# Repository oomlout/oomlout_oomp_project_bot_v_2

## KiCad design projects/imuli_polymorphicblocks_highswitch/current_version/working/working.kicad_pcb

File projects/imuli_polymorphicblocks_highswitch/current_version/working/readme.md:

# polymorphicblocks
 
## summary 
* id: imuli_polymorphicblocks_highswitch
* user: imuli
* name: polymorphicblocks
* board: highswitch
* repo: https://github.com/imuli/PolymorphicBlocks
* src_file_repo_kicad_pcb: examples/HighSwitch/HighSwitch.kicad_pcb
* src_file_repo_kicad_pcb_link: https://github.com/imuli/PolymorphicBlocks/tree/master/examples/HighSwitch/HighSwitch.kicad_pcb

* src_file_repo_sch: 
* src_file_repo_sch_link: https://github.com/imuli/PolymorphicBlocks/tree/master/
* full details link: https://github.com/oomlout/oomlout_oomp_project_bot_v_2/tree/main/projects/imuli_polymorphicblocks_highswitch/current_version/working

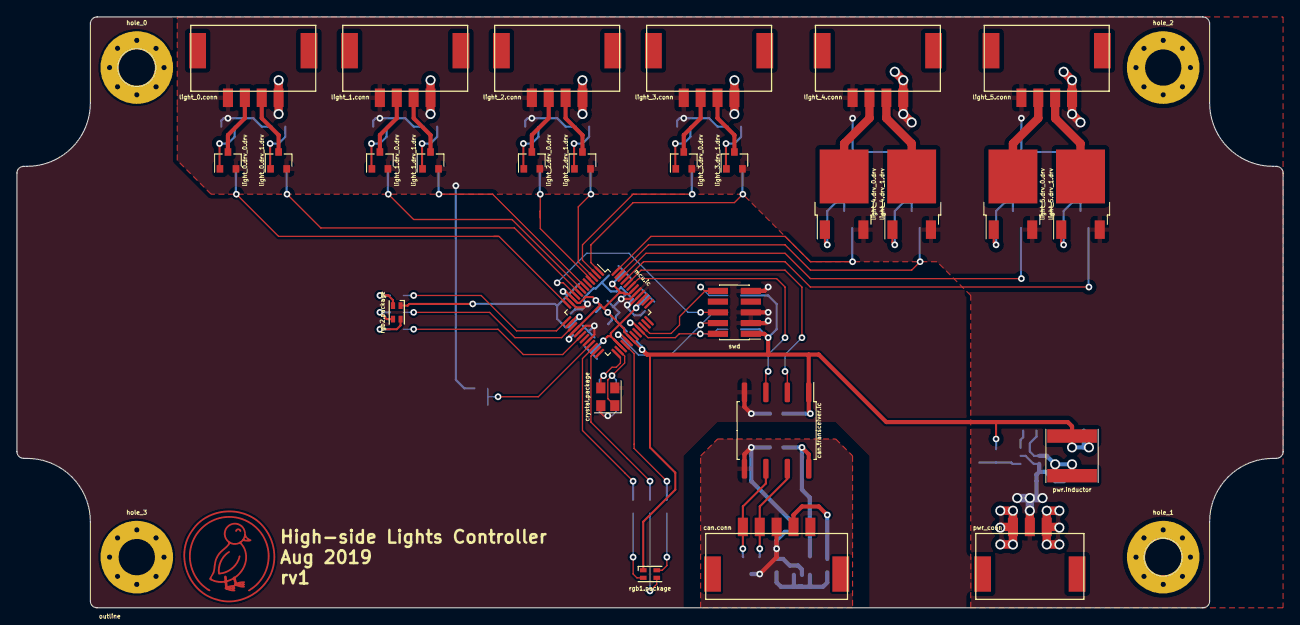
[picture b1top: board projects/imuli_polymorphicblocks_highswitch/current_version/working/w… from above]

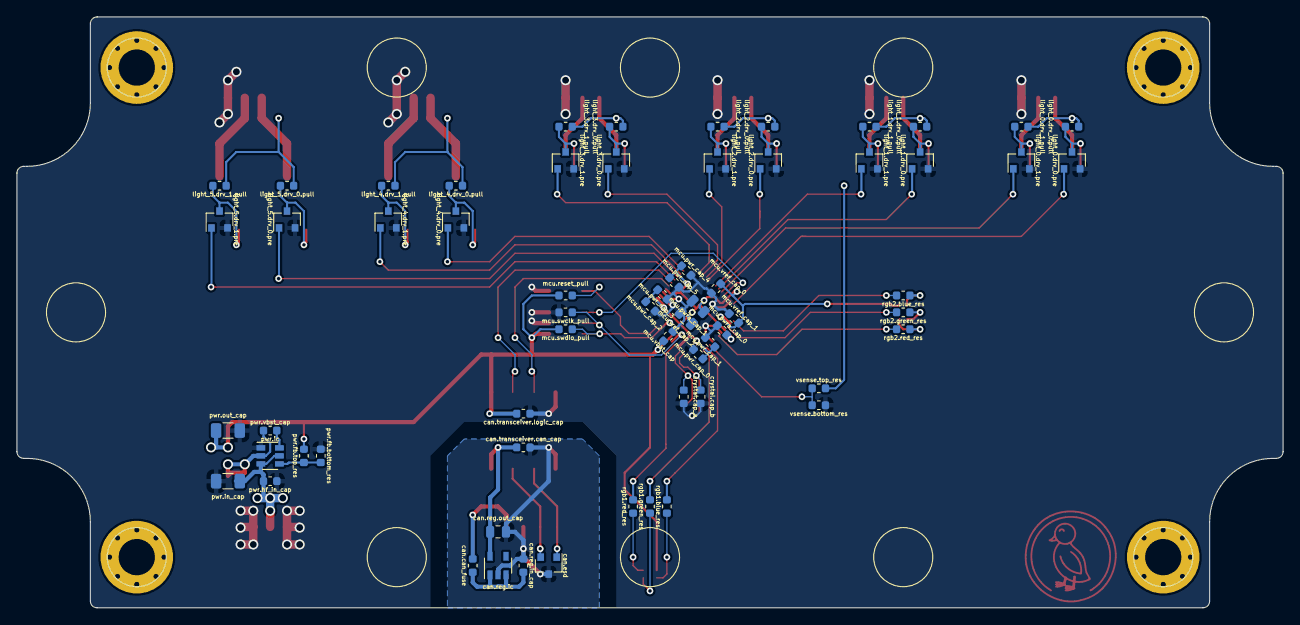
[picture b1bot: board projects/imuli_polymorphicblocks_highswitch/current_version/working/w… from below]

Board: 2 copper layers, 150.0 x 70.0 mm, 96 parts (63 on the bottom side), 69 nets.

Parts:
can.can_fuse: 0ZCM0005FF2G; R_0603_1608Metric
can.conn: Duraclik; Molex_DuraClik_vert_5pin
can.esd: PESD1CAN,215; SOT-23
can.reg.ic: AP2204K-5.0; SOT-23-5
can.reg.in_cap: 1µF, 25V, CL10A105KA8NNNC (C=(8.8e-07, 1.32e-06) 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; C_0603_1608Metric
can.reg.out_cap: 2.2µF, 10V, CL21B225KPFNNNE (C=(1.76e-06, 2.64e-0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; C_0805_2012Metric
can.transceiver.can_cap, can.transceiver.logic_cap: 0.1µF, 50V, CL10B104KB8NNNC (C=(8e-08, 1.2e-07) F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; C_0603_1608Metric
can.transceiver.ic: ISO1050DUB; SOP-8_6.62x9.15mm_P2.54mm
crystal.cap_a, crystal.cap_b: 18pF, 50V, CL10C180FB8NNNC (C=(1.764e-11, 1.836e-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; C_0603_1608Metric
crystal.package: 7V-12.000MAHE-T; Oscillator_SMD_Abracon_ASE-4Pin_3.2x2.5mm
duck: Duck; Duckling
hole_0, hole_1, hole_2, hole_3: M4; MountingHole_4.3mm_M4_Pad_Via
light_0.conn, light_1.conn, light_2.conn, light_3.conn, light_4.conn, light_5.conn: Duraclik; Molex_DuraClik_vert_4pin
light_0.drv_0.drv, light_0.drv_1.drv, light_1.drv_0.drv, light_1.drv_1.drv, light_2.drv_0.drv, light_2.drv_1.drv, light_3.drv_0.drv, light_3.drv_1.drv: DMP3099L-7 (Vds=(10.8, 13.200000000000001) V, Ids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; SOT-23
light_0.drv_0.pre, light_0.drv_1.pre, light_1.drv_0.pre, light_1.drv_1.pre, light_2.drv_0.pre, light_2.drv_1.pre, light_3.drv_0.pre, light_3.drv_1.pre, light_4.drv_0.pre, light_4.drv_1.pre, light_5.drv_0.pre, light_5.drv_1.pre: NX138AKR (Vds=(10.8, 13.200000000000001) V, Ids=(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; SOT-23
light_0.drv_0.pull, light_0.drv_1.pull, light_1.drv_0.pull, light_1.drv_1.pull, light_2.drv_0.pull, light_2.drv_1.pull, light_3.drv_0.pull, light_3.drv_1.pull, light_4.drv_0.pull, light_4.drv_1.pull, light_5.drv_0.pull, light_5.drv_1.pull: 10000, 1%, 0.1W (R=(9900.0, 10100.0) Ohm, P=(0.0,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; R_0603_1608Metric
light_4.drv_0.drv, light_4.drv_1.drv, light_5.drv_0.drv, light_5.drv_1.drv: TSM7P06CP ROG (Vds=(10.8, 13.200000000000001) V, 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; TO-252-2
mcu.ic: LPC1549JBD48; LQFP-48_7x7mm_P0.5mm
mcu.pwr_cap_0, mcu.pwr_cap_2, mcu.pwr_cap_4, mcu.pwra_cap_0, mcu.vbat_cap, mcu.vref_cap_0, mcu.vref_cap_1: 0.1µF, 50V, CL10B104KB8NNNC (C=(8e-08, 1.2e-07) F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; C_0603_1608Metric
mcu.pwr_cap_1, mcu.pwr_cap_3, mcu.pwr_cap_5: 10000pF, 50V, CL10B103KB8NNNC (C=(8e-09, 1.2e-08)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; C_0603_1608Metric
mcu.pwra_cap_1, mcu.vref_cap_2: 10µF, 10V, CL21A106KPFNNNG (C=(8e-06, 1.199999999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; C_0805_2012Metric
mcu.reset_pull: 10000, 1%, 0.1W (R=(9500.0, 10500.0) Ohm, P=(0.0,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; R_0603_1608Metric
mcu.swclk_pull, mcu.swdio_pull: 10000, 1%, 0.1W (R=(9500.0, 105000.0) Ohm, P=(0.0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; R_0603_1608Metric
outline: PN1332_Panel; Outline_150mm_70mm_PNX-91432
pwr.fb.bottom_res: 10000, 1%, 0.1W (R=(9900.0, 10100.0) Ohm, P=(0.0,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; R_0603_1608Metric
pwr.fb.top_res: 33000, 1%, 0.1W (R=(32670.0, 33330.0) Ohm, P=(0.0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; R_0603_1608Metric
pwr.hf_in_cap, pwr.vbst_cap: 0.1µF, 50V, CL10B104KB8NNNC (C=(8e-08, 1.2e-07) F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; C_0603_1608Metric
pwr.ic: TPS561201; SOT-23-6
pwr.in_cap: 22µF, 16V, CL31A226MOCLNNC (C=(7.498403575989784e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; C_1206_3216Metric
pwr.inductor: 10µH, 2.5A, NR6045T100M (L=(4.6396372126436784e-0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; L_Taiyo-Yuden_NR-60xx
pwr.out_cap: 22µF, 6.3V, CL31A226MQHNNNE (C=(1.034482758620689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; C_1206_3216Metric
pwr_conn: Duraclik; Molex_DuraClik_vert_3pin
rgb1.blue_res, rgb1.green_res, rgb1.red_res, rgb2.blue_res, rgb2.green_res, rgb2.red_res: 1000, 1%, 0.1W (R=(950.0, 1050.0) Ohm, P=(0.0, 0.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; R_0603_1608Metric
rgb1.package, rgb2.package: LED_RGB_0606
swd: SWD; PinHeader_2x05_P1.27mm_Vertical_SMD
vsense.bottom_res: 1500, 1%, 0.1W (R=(1485.0, 1515.0) Ohm, P=(0.0, 0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; R_0603_1608Metric
vsense.top_res: 4700, 1%, 0.1W (R=(4653.0, 4747.0) Ohm, P=(0.0, 0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; R_0603_1608Metric

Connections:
can.can.canh: can.conn.4, can.esd.2, can.transceiver.ic.7
can.can.canl: can.conn.5, can.esd.1, can.transceiver.ic.6
can.can_gnd: can.conn.3, can.esd.3, can.reg.ic.2, can.reg.in_cap.2, can.reg.out_cap.2, can.transceiver.can_cap.2, can.transceiver.ic.5
can.can_pwr: can.can_fuse.1, can.conn.2
can.controller.txd: can.transceiver.ic.3, mcu.ic.43
can.reg.pwr_in: can.can_fuse.2, can.reg.ic.1, can.reg.ic.3, can.reg.in_cap.1
can.reg.pwr_out: can.reg.ic.5, can.reg.out_cap.1, can.transceiver.can_cap.1, can.transceiver.ic.8
crystal.crystal.b: crystal.cap_b.1, crystal.package.3, mcu.ic.25
gnd: can.transceiver.ic.4, can.transceiver.logic_cap.2, crystal.cap_a.2, crystal.cap_b.2, crystal.package.2, crystal.package.4, light_0.conn.4, light_0.drv_0.pre.2, light_0.drv_1.pre.2, light_1.conn.4, light_1.drv_0.pre.2, light_1.drv_1.pre.2, light_2.conn.4, light_2.drv_0.pre.2, light_2.drv_1.pre.2, light_3.conn.4, light_3.drv_0.pre.2, light_3.drv_1.pre.2, light_4.conn.4, light_4.drv_0.pre.2, light_4.drv_1.pre.2, light_5.conn.4, light_5.drv_0.pre.2, light_5.drv_1.pre.2, mcu.ic.11, mcu.ic.17, mcu.ic.20, mcu.ic.40, mcu.ic.41, mcu.pwr_cap_0.2, mcu.pwr_cap_1.2, mcu.pwr_cap_2.2, mcu.pwr_cap_3.2, mcu.pwr_cap_4.2, mcu.pwr_cap_5.2, mcu.pwra_cap_0.2, mcu.pwra_cap_1.2, mcu.swclk_pull.1, mcu.vbat_cap.2, mcu.vref_cap_0.2, mcu.vref_cap_1.2, mcu.vref_cap_2.2, pwr.fb.bottom_res.2, pwr.hf_in_cap.2, pwr.ic.1, pwr.in_cap.2, pwr.out_cap.2, pwr_conn.1, pwr_conn.3, swd.3, swd.5, swd.9, vsense.bottom_res.2
light_0.conn.out_0: light_0.conn.2, light_0.drv_0.drv.3
light_0.control_0: light_0.drv_0.pre.1, mcu.ic.12
light_0.drv_0.drv.gate: light_0.drv_0.drv.1, light_0.drv_0.pre.3, light_0.drv_0.pull.2
light_0.drv_1.output: light_0.conn.3, light_0.drv_1.drv.3
light_0.drv_1.pull.2: light_0.drv_1.drv.1, light_0.drv_1.pre.3, light_0.drv_1.pull.2
light_1.conn.out_0: light_1.conn.2, light_1.drv_0.drv.3
light_1.conn.out_1: light_1.conn.3, light_1.drv_1.drv.3
light_1.control_0: light_1.drv_0.pre.1, mcu.ic.7
light_1.drv_0.drv.gate: light_1.drv_0.drv.1, light_1.drv_0.pre.3, light_1.drv_0.pull.2
light_1.drv_1.drv.1: light_1.drv_1.drv.1, light_1.drv_1.pre.3, light_1.drv_1.pull.2
light_2.conn.out_1: light_2.conn.3, light_2.drv_1.drv.3
light_2.control_1: light_2.drv_1.pre.1, mcu.ic.3
light_2.drv_0.output: light_2.conn.2, light_2.drv_0.drv.3
light_2.drv_0.pull.2: light_2.drv_0.drv.1, light_2.drv_0.pre.3, light_2.drv_0.pull.2
light_2.drv_1.drv.gate: light_2.drv_1.drv.1, light_2.drv_1.pre.3, light_2.drv_1.pull.2
light_3.conn.3: light_3.conn.3, light_3.drv_1.drv.3
light_3.drv_0.output: light_3.conn.2, light_3.drv_0.drv.3
light_3.drv_0.pre.drain: light_3.drv_0.drv.1, light_3.drv_0.pre.3, light_3.drv_0.pull.2
light_3.drv_1.drv.1: light_3.drv_1.drv.1, light_3.drv_1.pre.3, light_3.drv_1.pull.2
light_4.conn.out_1: light_4.conn.3, light_4.drv_1.drv.2
light_4.control_0: light_4.drv_0.pre.1, mcu.ic.48
light_4.drv_0.drv.gate: light_4.drv_0.drv.1, light_4.drv_0.pre.3, light_4.drv_0.pull.2
light_4.drv_0.output: light_4.conn.2, light_4.drv_0.drv.2
light_4.drv_1.drv.1: light_4.drv_1.drv.1, light_4.drv_1.pre.3, light_4.drv_1.pull.2
light_5.conn.2: light_5.conn.2, light_5.drv_0.drv.2
light_5.conn.out_1: light_5.conn.3, light_5.drv_1.drv.2
light_5.control_0: light_5.drv_0.pre.1, mcu.ic.46
light_5.control_1: light_5.drv_1.pre.1, mcu.ic.45
light_5.drv_0.pull.b: light_5.drv_0.drv.1, light_5.drv_0.pre.3, light_5.drv_0.pull.2
light_5.drv_1.pre.3: light_5.drv_1.drv.1, light_5.drv_1.pre.3, light_5.drv_1.pull.2
mcu.can_0.rxd: can.transceiver.ic.2, mcu.ic.44
mcu.digital_4: light_4.drv_1.pre.1, mcu.ic.47
mcu.digital_6: light_3.drv_1.pre.1, mcu.ic.1
mcu.digital_7: light_3.drv_0.pre.1, mcu.ic.2
mcu.digital_9: light_2.drv_0.pre.1, mcu.ic.4
mcu.digital_10: light_1.drv_1.pre.1, mcu.ic.6
mcu.digital_12: light_0.drv_1.pre.1, mcu.ic.8
mcu.digital_15: mcu.ic.15, rgb2.green_res.2
mcu.digital_16: mcu.ic.18, rgb2.red_res.2
mcu.digital_18: mcu.ic.23, rgb1.green_res.2
mcu.xtal.xtal_in: crystal.cap_a.1, crystal.package.1, mcu.ic.26
pwr.ic.4: pwr.fb.bottom_res.1, pwr.fb.top_res.2, pwr.ic.4
pwr.sw: pwr.ic.2, pwr.inductor.1, pwr.vbst_cap.2
pwr.vbst_cap.1: pwr.ic.6, pwr.vbst_cap.1
rgb1.blue: mcu.ic.22, rgb1.blue_res.2
rgb1.blue_res.a: rgb1.blue_res.1, rgb1.package.2
rgb1.package.3: rgb1.green_res.1, rgb1.package.3
rgb1.package.4: rgb1.package.4, rgb1.red_res.1
rgb1.red: mcu.ic.28, rgb1.red_res.2
rgb2.blue: mcu.ic.13, rgb2.blue_res.2
rgb2.blue_res.a: rgb2.blue_res.1, rgb2.package.2
rgb2.package.3: rgb2.green_res.1, rgb2.package.3
rgb2.package.4: rgb2.package.4, rgb2.red_res.1
swd.2: mcu.ic.33, mcu.swdio_pull.2, swd.2
swd.4: mcu.ic.29, mcu.swclk_pull.2, swd.4
swd.6: mcu.ic.9, swd.6
swd.10: mcu.ic.34, mcu.reset_pull.2, swd.10
v3v3: can.transceiver.ic.1, can.transceiver.logic_cap.1, mcu.ic.10, mcu.ic.14, mcu.ic.16, mcu.ic.27, mcu.ic.30, mcu.ic.39, mcu.ic.42, mcu.pwr_cap_0.1, mcu.pwr_cap_1.1, mcu.pwr_cap_2.1, mcu.pwr_cap_3.1, mcu.pwr_cap_4.1, mcu.pwr_cap_5.1, mcu.pwra_cap_0.1, mcu.pwra_cap_1.1, mcu.reset_pull.1, mcu.swdio_pull.1, mcu.vbat_cap.1, mcu.vref_cap_0.1, mcu.vref_cap_1.1, mcu.vref_cap_2.1, pwr.fb.top_res.1, pwr.inductor.2, pwr.out_cap.1, rgb1.package.1, rgb2.package.1, swd.1
vin: light_0.conn.1, light_0.drv_0.drv.2, light_0.drv_0.pull.1, light_0.drv_1.drv.2, light_0.drv_1.pull.1, light_1.conn.1, light_1.drv_0.drv.2, light_1.drv_0.pull.1, light_1.drv_1.drv.2, light_1.drv_1.pull.1, light_2.conn.1, light_2.drv_0.drv.2, light_2.drv_0.pull.1, light_2.drv_1.drv.2, light_2.drv_1.pull.1, light_3.conn.1, light_3.drv_0.drv.2, light_3.drv_0.pull.1, light_3.drv_1.drv.2, light_3.drv_1.pull.1, light_4.conn.1, light_4.drv_0.drv.3, light_4.drv_0.pull.1, light_4.drv_1.drv.3, light_4.drv_1.pull.1, light_5.conn.1, light_5.drv_0.drv.3, light_5.drv_0.pull.1, light_5.drv_1.drv.3, light_5.drv_1.pull.1, pwr.hf_in_cap.1, pwr.ic.3, pwr.ic.5, pwr.in_cap.1, pwr_conn.2, vsense.top_res.1
vsense.out: mcu.ic.21, vsense.bottom_res.1, vsense.top_res.2

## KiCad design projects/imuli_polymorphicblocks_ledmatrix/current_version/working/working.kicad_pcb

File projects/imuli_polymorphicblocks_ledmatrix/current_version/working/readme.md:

# polymorphicblocks
 
## summary 
* id: imuli_polymorphicblocks_ledmatrix
* user: imuli
* name: polymorphicblocks
* board: ledmatrix
* repo: https://github.com/imuli/PolymorphicBlocks
* src_file_repo_kicad_pcb: examples/LedMatrix/LedMatrix.kicad_pcb
* src_file_repo_kicad_pcb_link: https://github.com/imuli/PolymorphicBlocks/tree/master/examples/LedMatrix/LedMatrix.kicad_pcb

* src_file_repo_sch: 
* src_file_repo_sch_link: https://github.com/imuli/PolymorphicBlocks/tree/master/
* full details link: https://github.com/oomlout/oomlout_oomp_project_bot_v_2/tree/main/projects/imuli_polymorphicblocks_ledmatrix/current_version/working

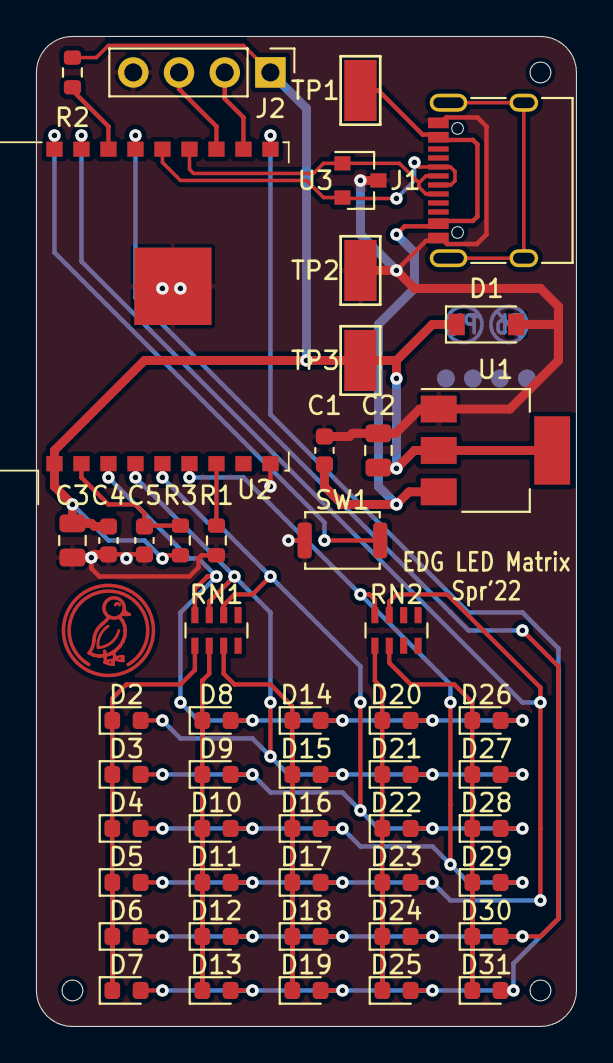
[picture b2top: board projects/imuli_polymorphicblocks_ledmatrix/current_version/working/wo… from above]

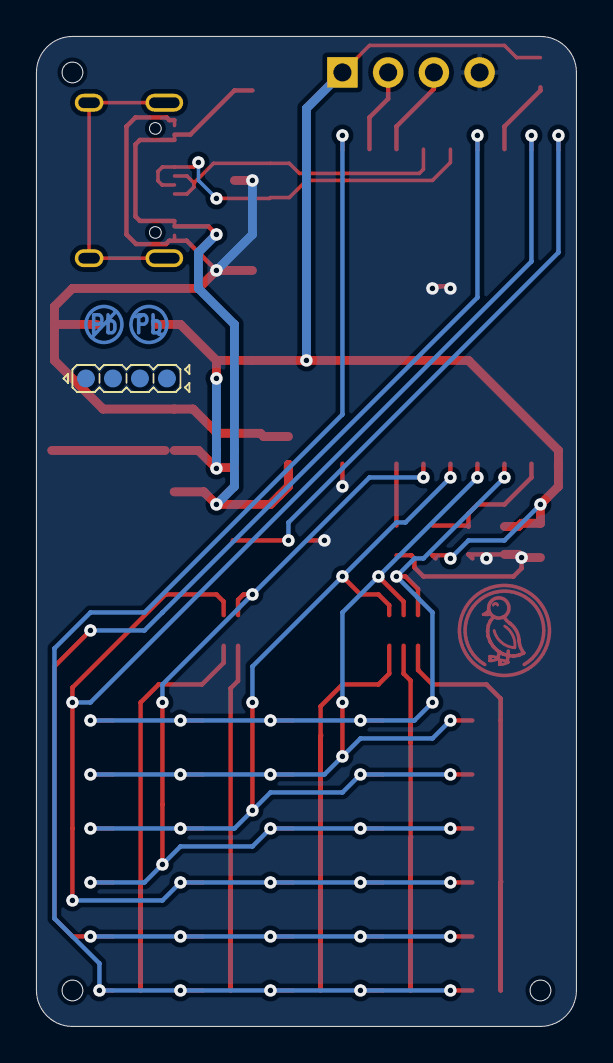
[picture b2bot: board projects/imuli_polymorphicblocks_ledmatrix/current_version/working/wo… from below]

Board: 2 copper layers, 30.0 x 55.0 mm, 56 parts (2 on the bottom side), 23 nets.

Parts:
1: Indicator_LeadFree
2: Indicator_IdDots_4
C1, C4: C14663; C_0603_1608Metric
C2: C1779; C_0805_2012Metric
C3: C15850; C_0805_2012Metric
C5: C15849; C_0603_1608Metric
D1: C499796; D_SOD-123
D2, D3, D4, D5, D6, D7, D8, D9, D10, D11, D12, D13, D14, D15, D16, D17, D18, D19, D20, D21, D22, D23, D24, D25, D26, D27, D28, D29, D30, D31: C72038; LED_0603_1608Metric
H1, H2, H3: JlcToolingHole_1.152mm
J1: C165948; USB_C_Receptacle_XKB_U262-16XN-4BVC11
J2: PinHeader_1x04_P2.54mm_Vertical
R1, R2, R3: C25804; R_0603_1608Metric
RN1, RN2: C425057; R_Array_Concave_4x0603
SW1: SW_Push_SPST_NO_Alps_SKRK
TP1, TP2, TP3: C238130; TestPoint_Keystone_5015_Micro-Minature
U1: C86781; SOT-223-3_TabPin2
U2: C2934560; ESP-WROOM-02
U3: C87911; SOT-23
U4: Symbol_Duckling

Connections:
gnd: C1.2, C2.2, C3.2, C4.2, C5.2, D1.2, J1.A1, J1.A12, J1.B1, J1.B12, J2.4, R1.1, SW1.1, TP2.1, U1.1, U2.9, U2.19, U3.3
matrix.ios.5: D6.2, D12.2, D18.2, D24.2, D30.2, U2.15
matrix.ios.6: D7.2, D13.2, D19.2, D25.2, D31.2, U2.10
matrix_res1.a.0: D2.1, D3.1, D4.1, D5.1, D6.1, D7.1, RN1.1
matrix_res1.a.1: D8.1, D9.1, D10.1, D11.1, D12.1, D13.1, RN1.2
matrix_res1.a.2: D14.1, D15.1, D16.1, D17.1, D18.1, D19.1, RN1.3
matrix_res1.b.1: D2.2, D15.2, D21.2, D27.2, RN1.7, U2.4
matrix_res2.a.0: D20.1, D21.1, D22.1, D23.1, D24.1, D25.1, RN2.1
matrix_res2.a.1: D26.1, D27.1, D28.1, D29.1, D30.1, D31.1, RN2.2
mcu.en_pull.output: C5.1, R3.2, U2.2
mcu.gpio.led_0: D8.2, D14.2, D20.2, D26.2, RN1.8, U2.3
mcu.gpio.led_2: D3.2, D9.2, D22.2, D28.2, RN1.6, U2.5
mcu.gpio.led_3: D4.2, D10.2, D16.2, D29.2, RN2.8, U2.6
mcu.gpio.led_4: D5.2, D11.2, D17.2, D23.2, RN2.7, U2.17
mcu.gpio.sw1: SW1.2, U2.18
mcu.ic.uart0.rx: J2.2, U2.11
mcu.io2_pull.io: R2.2, U2.16
mcu.io8_pull.b: R1.2, U2.7
mcu.uart0.uart.rx: J2.3, U2.12
usb.usb.dp: J1.A6, J1.B6, U2.14, U3.2
usb_esd.usb.dm: J1.A7, J1.B7, U2.13, U3.1
v3v3: C2.1, C3.1, C4.1, D1.1, J2.1, R2.1, R3.1, TP3.1, U1.2, U2.1
vusb: C1.1, J1.A4, J1.A9, J1.B4, J1.B9, TP1.1, U1.3

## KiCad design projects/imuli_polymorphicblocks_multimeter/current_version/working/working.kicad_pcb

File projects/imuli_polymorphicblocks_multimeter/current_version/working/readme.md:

# polymorphicblocks
 
## summary 
* id: imuli_polymorphicblocks_multimeter
* user: imuli
* name: polymorphicblocks
* board: multimeter
* repo: https://github.com/imuli/PolymorphicBlocks
* src_file_repo_kicad_pcb: examples/Multimeter/Multimeter.kicad_pcb
* src_file_repo_kicad_pcb_link: https://github.com/imuli/PolymorphicBlocks/tree/master/examples/Multimeter/Multimeter.kicad_pcb

* src_file_repo_sch: 
* src_file_repo_sch_link: https://github.com/imuli/PolymorphicBlocks/tree/master/
* full details link: https://github.com/oomlout/oomlout_oomp_project_bot_v_2/tree/main/projects/imuli_polymorphicblocks_multimeter/current_version/working

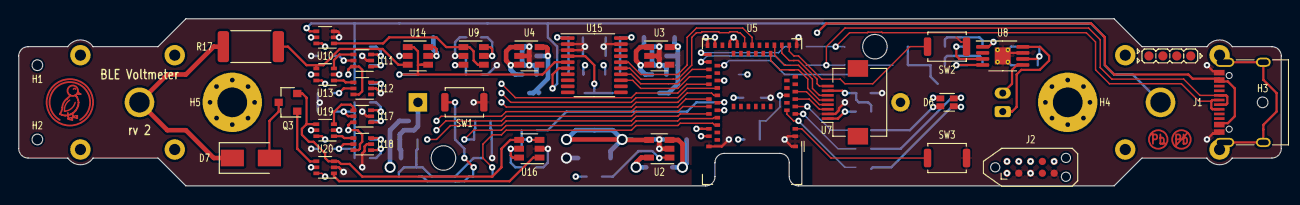
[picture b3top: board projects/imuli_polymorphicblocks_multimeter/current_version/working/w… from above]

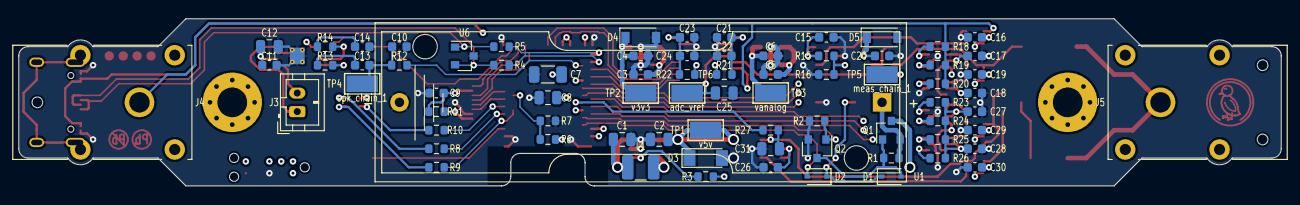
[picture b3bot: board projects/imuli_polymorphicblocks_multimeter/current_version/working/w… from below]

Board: 4 copper layers, 136.0 x 18.0 mm, 111 parts (76 on the bottom side), 80 nets.

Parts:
1: LeadFree; Indicator_LeadFree
2: IdDots4; Indicator_IdDots_4
C1, C8, C25: X5R 25V ±10% 10uF 0805 Multilayer Ceramic Capacit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; C_0805_2012Metric
C2, C12: 25V 4.7uF X5R ±10% 0805 Multilayer Ceramic Capaci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; C_0805_2012Metric
C3, C4, C5, C6, C9, C13, C14: 50V 1uF X5R ±10% 0603 Multilayer Ceramic Capacito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; C_0603_1608Metric
C7: 50V 10uF X5R ±10% 1206 Multilayer Ceramic Capacit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; C_1206_3216Metric
C10: 50V 47nF X7R ±10% 0603 Multilayer Ceramic Capacit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; C_0603_1608Metric
C11, C15, C16, C17, C18, C19, C20, C21, C22, C23, C24, C26, C27, C28, C29, C30: 50V 100nF X7R ±10% 0603 Multilayer Ceramic Capaci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; C_0603_1608Metric
C31: 50V 2.2uF Y5V ±20% 0805 Multilayer Ceramic Capaci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; C_0805_2012Metric
D1, D2: 30V 370mV@1mA 30mA SOD-323 Schottky Barrier Diode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; D_SOD-323
D3: 100nA@1V 25Ω Single 5.2V~{6V} 500mW 5.6V LL-34 Ze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; D_MiniMELF
D4, D5: 5μA@1V 90Ω Single 3.6V~{3.8V} 350mW 3.4V SOD-123 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; D_SOD-123
D6: LED_LiteOn_LTST-C19HE1WT
D7: DIODE GEN PURP 400V 1A DO214AC; D_SMA
H1, H2, H3: JlcToolingHole_1.152mm
H4, H5: M3; MountingHole_3.2mm_M3_Pad_Via
J1: USB_C_Receptacle_XKB_U262-16XN-4BVC11
J2: SWD; Tag-Connect_TC2050-IDC-NL_2x05_P1.27mm_Vertical
J3: JST_PH_B2B-PH-K_1x02_P2.00mm_Vertical
J4, J5: CLIFF_FCR7350
L1: 620mA 22uH ±10% 270mΩ 1210 Inductors (SMD) ROHS; L_1210_3225Metric
Q1: 20V 3.1A 860mW 112mΩ@4.5V,2.8A 1V@250μA P Channel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; SOT-23
Q2: 60V 115mA 200mW 7.5Ω@10V,500mA 2.5V@250μA N Chann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; SOT-23
Q3: MOSFET P-CH 250V 140MA SC-59-3; SOT-23
R1, R2, R3, R6, R7, R8, R9, R10, R12, R13, R14, R15, R16, R18, R19, R20, R23, R24, R25, R26, R27: ±1% 1/10W Thick Film Resistors 75V ±100ppm/℃ -55℃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; R_0603_1608Metric
R4, R5, R11: ±1% 1/10W Thick Film Resistors 75V ±200ppm/℃ -55℃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; R_0603_1608Metric
R17: 1M, 1%, 1.0 W; R_2512_6332Metric
R21, R22: ±1% 1/10W Thick Film Resistors 75V ±400ppm/℃ -55℃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; R_0603_1608Metric
SW1, SW2, SW3: SW_Push_SPST_NO_Alps_SKRK
TP1: v5v; TestPoint_Keystone_5015_Micro-Minature
TP2: v3v3; TestPoint_Keystone_5015_Micro-Minature
TP3: vanalog; TestPoint_Keystone_5015_Micro-Minature
TP4: spk_chain_1; TestPoint_Keystone_5015_Micro-Minature
TP5: meas_chain_1; TestPoint_Keystone_5015_Micro-Minature
TP6: adc_vref; TestPoint_Keystone_5015_Micro-Minature
U1: BatteryHolder_Keystone_2460_1xAA
U2, U3, U4: SOT-23-5
U5: Raytac_MDBT50Q
U6: SOT-23
U7: Hirose_FH12-8S-0.5SH_1x08-1MP_P0.50mm_Horizontal
U8: MSOP-8-1EP_3x3mm_P0.65mm_EP1.73x1.85mm_ThermalVias
U9, U14, U16: SOT-23-6
U10, U11, U12, U13, U17, U18, U19, U20: SOT-363_SC-70-6
U15: TSSOP-20_4.4x6.5mm_P0.65mm
U21: Duck; Symbol_Duckling

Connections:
(adapter)inp.port.src: D7.1, J5.1, R17.1
adc.dvdd_res.b: C23.1, C24.1, R22.2, U15.20
adc.ic.avdd: C21.1, C22.1, R21.2, U15.1
adc.spi.miso: U5.24, U15.16
adc.spi.mosi: U5.26, U15.15
adc.spi.sck: U5.37, U15.14
adc_vref: C25.1, TP6.1, U15.4
data_usb.A4: C7.1, J1.A4, J1.A9, J1.B4, J1.B9, U5.32
data_usb.usb.dm: J1.A7, J1.B7, R5.2, U6.1
data_usb.usb.dp: J1.A6, J1.B6, R4.2, U6.2
driver.control: C31.1, R27.2, U16.3
driver.fet.drain: D7.2, Q3.3
driver.range.switch.inputs.0: R23.2, U17.3
driver.range.switch.inputs.1: R24.2, U17.1
driver.range.switch.inputs.2: R25.2, U18.3
driver.range.switch.inputs.3: R26.2, U18.1
driver.range.switch.sw[1_0].inputs.0: U17.4, U19.3
driver.range.switch.sw[1_0].inputs.1: U18.4, U19.1
driver.select.0_0: U5.46, U17.6, U18.6
driver.sw.inputs.0: Q3.2, U16.4, U19.4, U20.3
driver.sw.inputs.1: U16.1, U20.1
driver.sw.out: Q3.1, U20.4
gate.amp_fet.drain: D1.2, Q1.1, Q2.3, R1.2
gate.ctl_diode.cathode: D1.1, D2.1, SW1.2
gate.pwr_out: C1.1, L1.1, Q1.3, R3.1, R6.1, U2.3
gnd: C1.2, C2.2, C3.2, C4.2, C5.2, C6.2, C7.2, C8.2, C9.2, C10.2, C11.2, C12.2, C14.2, C15.2, C16.2, C17.2, C18.2, C19.2, C20.2, C21.2, C22.2, C23.2, C24.2, C25.2, C26.2, C27.2, C28.2, C29.2, C30.2, C31.2, D3.2, D4.2, D5.2, J1.A1, J1.A12, J1.B1, J1.B12, J2.2, J2.3, J2.5, Q2.2, R2.2, R7.2, R16.2, SW1.1, SW2.1, SW3.1, U1.2, U2.2, U3.2, U4.2, U5.1, U5.2, U5.15, U5.33, U5.55, U6.3, U7.2, U8.7, U8.9, U9.2, U10.2, U10.3, U11.2, U12.2, U13.2, U14.2, U15.2, U15.3, U15.19, U16.2, U17.2, U18.2, U19.2, U20.2
inn_merge.inputs.0: J4.1, R18.1, R19.1, R20.1, U10.4, U15.6
inn_mux.control.0: U5.41, U10.6
lcd.led_res.b: R11.2, U7.1
lcd.spi.mosi: U5.19, U7.5
lcd.spi.sck: U5.18, U7.6
mcu.adc.vbatsense: R6.2, R7.1, U5.9
mcu.gpio.adc_cs: U5.39, U15.13
mcu.gpio.driver_control: R27.1, U5.45
mcu.gpio.driver_enable: U5.48, U20.6
mcu.gpio.driver_select_1_0: U5.44, U19.6
mcu.gpio.gate_control: Q2.1, R2.1, U5.49
mcu.gpio.lcd_cs: U5.17, U7.8
mcu.gpio.lcd_reset: U5.8, U7.3
mcu.gpio.lcd_rs: U5.10, U7.4
mcu.gpio.measure_select_0_0: U5.42, U11.6, U12.6
mcu.gpio.measure_select_1_0: U5.43, U13.6
mcu.gpio.rgb_blue: R10.2, U5.6
mcu.gpio.sw0: D2.2, U5.50
mcu.gpio.sw1: SW2.2, U5.16
mcu.gpio.sw2: SW3.2, U5.3
mcu.ic.swd.reset: J2.6, U5.40
mcu.ic.swd.swdio: J2.10, U5.51
mcu.swd.swd.swclk: J2.9, U5.53
mcu.swd.swd.swo: J2.8, U5.47
mcu.usb_res.usb_inner.dm: R5.1, U5.34
mcu.usb_res.usb_inner.dp: R4.1, U5.35
meas_chain_0: R17.2, U13.4, U14.3
meas_chain_1: TP5.1, U14.1, U14.4, U15.5
measure.range.switch.inputs.0: R18.2, U11.3
measure.range.switch.inputs.1: R19.2, U11.1
measure.range.switch.inputs.2: R20.2, U12.3
measure.range.switch.sw[1_0].inputs.0: U11.4, U13.3
measure.range.switch.sw[1_0].inputs.1: U12.4, U13.1
ref_buf.inp: R15.2, R16.1, U9.3
reg_5v.ic.ce: R3.2, U2.1
reg_5v.power_path.switch: L1.2, U2.5
rgb.blue_res.a: D6.1, R10.1
rgb.green_res.a: D6.4, R9.1
rgb.red_res.a: D6.3, R8.1
rgb.signals.green: R9.2, U5.5
rgb.signals.red: R8.2, U5.4
spk_chain_0: R12.1, U5.36
spk_chain_1: C10.1, C13.2, R12.2, TP4.1
spk_chain_2.a: J3.1, U8.8
spk_chain_2.b: J3.2, U8.5
spk_drv.(adapter)inp_res.b.dst: R13.2, U8.4
spk_drv.ic.inn: R14.2, U8.3
spk_drv.inn_res.a: C14.1, R14.1
spk_drv.inp_res.a: C13.1, R13.1
v3v3: C4.1, C8.1, C9.1, D4.1, D6.2, J2.1, R11.1, R22.1, TP2.1, U3.5, U5.28, U5.30, U7.7
v5v: C2.1, C3.1, C5.1, C11.1, C12.1, D3.1, TP1.1, U2.4, U3.1, U3.3, U4.1, U4.3, U8.1, U8.6
vanalog: C6.1, C15.1, C16.1, C17.1, C18.1, C19.1, C20.1, C26.1, C27.1, C28.1, C29.1, C30.1, D5.1, R15.1, R21.1, R23.1, R24.1, R25.1, R26.1, TP3.1, U4.5, U9.5, U9.6, U10.5, U11.5, U12.5, U13.5, U14.5, U14.6, U16.5, U16.6, U17.5, U18.5, U19.5, U20.5
vbat: Q1.2, R1.1, U1.1
vcenter: U9.1, U9.4, U10.1

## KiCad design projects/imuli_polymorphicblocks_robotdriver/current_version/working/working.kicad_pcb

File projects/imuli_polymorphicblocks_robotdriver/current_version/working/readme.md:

# polymorphicblocks
 
## summary 
* id: imuli_polymorphicblocks_robotdriver
* user: imuli
* name: polymorphicblocks
* board: robotdriver
* repo: https://github.com/imuli/PolymorphicBlocks
* src_file_repo_kicad_pcb: examples/RobotDriver/RobotDriver.kicad_pcb
* src_file_repo_kicad_pcb_link: https://github.com/imuli/PolymorphicBlocks/tree/master/examples/RobotDriver/RobotDriver.kicad_pcb

* src_file_repo_sch: 
* src_file_repo_sch_link: https://github.com/imuli/PolymorphicBlocks/tree/master/
* full details link: https://github.com/oomlout/oomlout_oomp_project_bot_v_2/tree/main/projects/imuli_polymorphicblocks_robotdriver/current_version/working

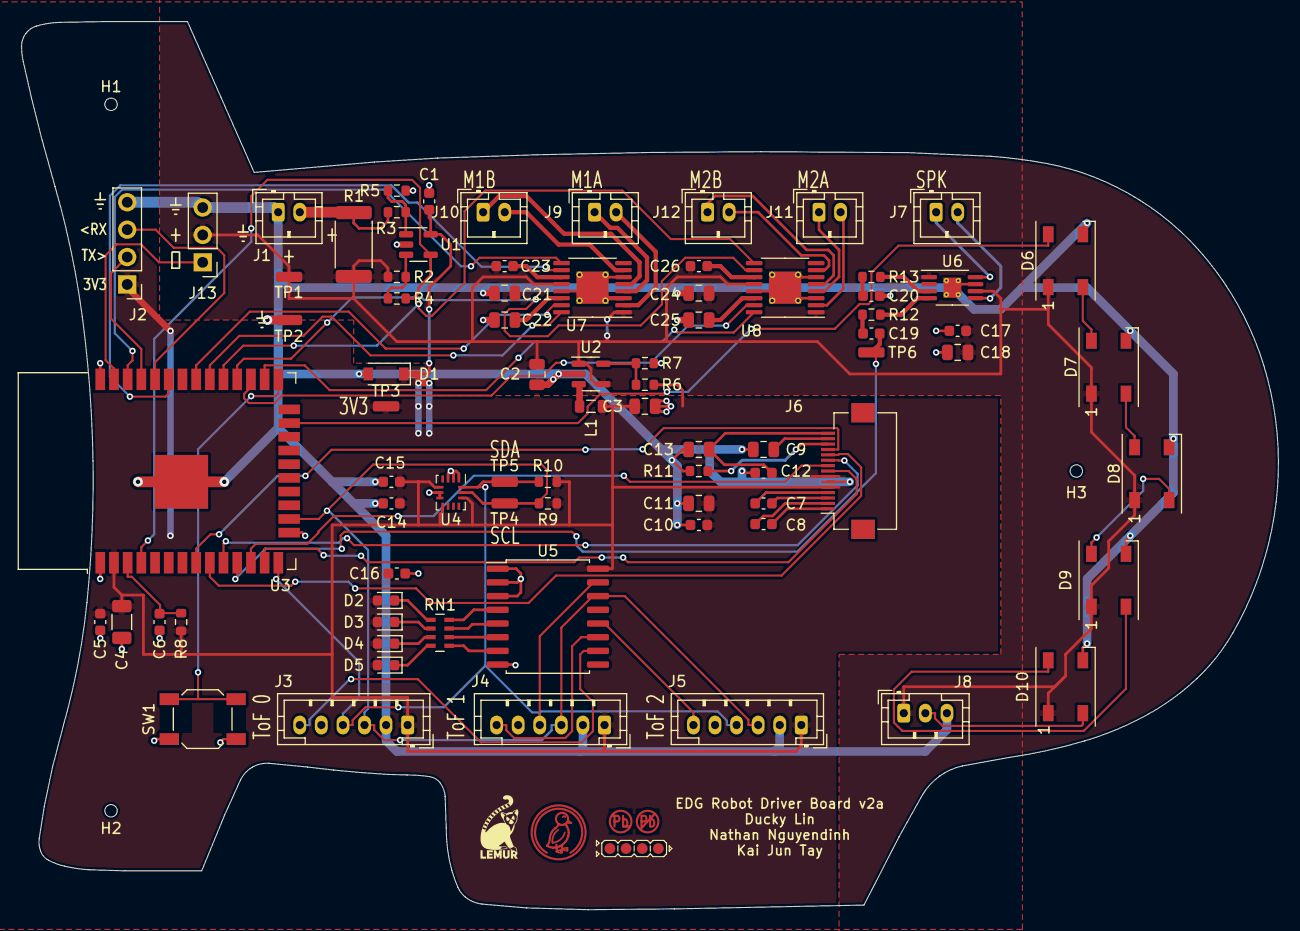
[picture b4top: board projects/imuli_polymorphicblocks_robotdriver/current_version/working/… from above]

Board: 2 copper layers, 116.5 x 82.3 mm, 86 parts (0 on the bottom side), 72 nets.

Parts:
C1, C5, C7, C8, C10, C12, C14, C15, C16, C17: C14663; C_0603_1608Metric
C2, C3, C9, C11, C18, C22, C25: C1779; C_0805_2012Metric
C4: C5672; C_1206_3216Metric
C6, C19, C20: C15849; C_0603_1608Metric
C13, C21, C24: C15850; C_0805_2012Metric
C23, C26: C57112; C_0603_1608Metric
D1: C499796; D_SOD-123
D2, D3, D4, D5: C2286; LED_0603_1608Metric
D6, D7, D8, D9, D10: C2920042; LED_WS2812B_PLCC4_5.0x5.0mm_P3.2mm
H1, H2, H3: JlcToolingHole_1.152mm
J1, J7, J9, J10, J11, J12: JST_PH_B2B-PH-K_1x02_P2.00mm_Vertical
J2: PinHeader_1x04_P2.54mm_Vertical
J3, J4, J5: JST_PH_B6B-PH-K_1x06_P2.00mm_Vertical
J6: Hirose_FH12-15S-0.5SH_1x15-1MP_P0.50mm_Horizontal
J8: JST_PH_B3B-PH-K_1x03_P2.00mm_Vertical
J13: PinHeader_1x03_P2.54mm_Vertical
L1: C98331; L_0805_2012Metric
R1: C305115; R_2512_6332Metric
R2, R3, R8: C25804; R_0603_1608Metric
R4, R5: C25811; R_0603_1608Metric
R6: C23231; R_0603_1608Metric
R7: C22809; R_0603_1608Metric
R9, R10: C23162; R_0603_1608Metric
R11: C23203; R_0603_1608Metric
R12, R13: C22984; R_0603_1608Metric
RN1: C20197; R_Array_Concave_4x0603
SW1: C318884; SW_SPST_SKQG_WithoutStem
TP1, TP2, TP3, TP4, TP5, TP6: TestPoint_TE_RCU_0603
U1: C7972; SOT-23-5
U2: C500769; SOT-23-5
U3: C701342; ESP32-WROOM-32
U4: C967633; Bosch_LGA-14_3x2.5mm_P0.5mm
U5: C86832; SOIC-16W_7.5x10.3mm_P1.27mm
U6: C27396; MSOP-8-1EP_3x3mm_P0.65mm_EP1.68x1.88mm_ThermalVias
U7, U8: C50506; TSSOP-16-1EP_4.4x5mm_P0.65mm_EP3x3mm_ThermalVias
U9: Symbol_LemurSmall
U10: Symbol_Duckling
U11: Indicator_LeadFree
U12: Indicator_IdDots_4

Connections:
batt.pins.2: J1.2, R1.1, R3.1
expander.io.led_1: RN1.7, U5.5
expander.io.led_2: RN1.6, U5.6
expander.io.tof_xshut_0: J3.6, U5.10
expander.io.tof_xshut_1: J4.6, U5.11
gnd: C1.2, C2.2, C3.2, C4.2, C5.2, C6.2, C9.2, C10.2, C11.2, C12.2, C13.2, C14.2, C15.2, C16.2, C17.2, C18.2, C20.2, C21.2, C22.2, C24.2, C25.2, D1.2, D6.3, D7.3, D8.3, D9.3, D10.3, J1.1, J2.4, J3.2, J4.2, J5.2, J6.6, J8.3, J13.3, R5.1, R7.2, R11.2, SW1.1, TP2.1, U1.2, U2.2, U3.1, U3.15, U3.38, U3.39, U4.1, U4.2, U4.3, U4.6, U4.7, U5.1, U5.2, U5.3, U5.8, U6.7, U6.9, U7.3, U7.6, U7.13, U7.17, U8.3, U8.6, U8.13, U8.17
i2c_chain_0.scl: J3.3, J4.3, J5.3, R9.2, TP4.1, U3.16, U4.13, U5.14
i2c_chain_0.sda: J3.4, J4.4, J5.4, R10.2, TP5.1, U3.14, U4.14, U5.15
isense.amp.(adapter)r2.b.src: R3.2, R5.2, U1.1
isense.amp.(adapter)rf.b.src: R2.2, R4.2, U1.3
lcd.c1_cap.pos: C7.1, J6.3
lcd.c2_cap.pos: C8.1, J6.1
lcd.device.c1n: C7.2, J6.4
lcd.device.c2n: C8.2, J6.2
lcd.device.iref: J6.13, R11.1
lcd.spi.mosi: J6.12, U3.8
lcd.spi.sck: J6.11, U3.9
lcd.vcc_cap2.pwr: C12.1, C13.1, J6.15
lcd.vcomh_cap.pos: C9.1, J6.14
led_pixel.pins.2: D10.2, J8.2
led_res.a.0: D2.1, RN1.1
led_res.a.1: D3.1, RN1.2
led_res.a.2: D4.1, RN1.3
led_res.a.3: D5.1, RN1.4
led_res.b.0: RN1.8, U5.4
leds.signals.3: RN1.5, U5.7
m1_a.pins.1: J9.1, U7.4
m1_a.pins.2: J9.2, U7.2
m1_b.pins.1: J10.1, U7.5
m1_b.pins.2: J10.2, U7.7
m2_a.pins.1: J11.1, U8.4
m2_a.pins.2: J11.2, U8.2
m2_b.pins.1: J12.1, U8.5
m2_b.pins.2: J12.2, U8.7
mcu.adc.isense: R4.1, U1.4, U3.4
mcu.gpio.lcd_cs: J6.8, U3.13
mcu.gpio.lcd_dc: J6.10, U3.10
mcu.gpio.lcd_reset: J6.9, U3.12
mcu.gpio.ledArray: D6.4, U3.23
mcu.gpio.motor_1a1: U3.30, U7.16
mcu.gpio.motor_1a2: U3.31, U7.15
mcu.gpio.motor_1b1: U3.36, U7.9
mcu.gpio.motor_1b2: U3.33, U7.10
mcu.gpio.motor_2a1: U3.26, U8.16
mcu.gpio.motor_2a2: U3.27, U8.15
mcu.gpio.motor_2b1: U3.29, U8.9
mcu.gpio.motor_2b2: U3.28, U8.10
mcu.ic.chip_pu: C6.1, R8.2, U3.3
mcu.ic.io0: SW1.2, U3.25
mcu.ic.uart0.tx: J2.2, U3.35
mcu.uart0.uart.tx: J2.3, U3.34
motor_driver1.ic.vcp: C23.1, U7.11
motor_driver1.vint_cap.pwr: C22.1, U7.14
motor_driver2.ic.vcp: C26.1, U8.11
motor_driver2.vint_cap.pwr: C25.1, U8.14
reg_3v3.fb.output: R6.2, R7.1, U2.5
reg_3v3.ic.sw: L1.1, U2.3
servo.pins.1: J13.1, U3.37
spk_chain_0: C19.2, TP6.1, U3.11
spk_chain_1.a: J7.1, U6.8
spk_chain_1.b: J7.2, U6.5
spk_drv.(adapter)inn_res.b.src: R13.2, U6.3
spk_drv.(adapter)inp_res.b.src: R12.2, U6.4
spk_drv.inn_cap.pos: C20.1, R13.1
spk_drv.inp_res.a: C19.1, R12.1
tof.xshut.2: J5.6, U5.12
v3v3: C1.1, C3.1, C4.1, C5.1, C10.1, C11.1, C14.1, C15.1, C16.1, D1.1, D2.2, D3.2, D4.2, D5.2, J2.1, J3.1, J4.1, J5.1, J6.5, J6.7, L1.2, R6.1, R8.1, R9.1, R10.1, TP3.1, U1.5, U3.2, U4.5, U4.8, U4.12, U5.16
vbatt: C2.1, C17.1, C18.1, C21.1, C23.2, C24.1, C26.2, D6.1, D7.1, D8.1, D9.1, D10.1, J8.1, J13.2, R1.2, R2.1, TP1.1, U2.1, U2.4, U6.1, U6.6, U7.1, U7.12, U8.1, U8.12
ws2812bArray.led[1].din: D6.2, D7.4
ws2812bArray.led[1].dout: D7.2, D8.4
ws2812bArray.led[3].din: D8.2, D9.4
ws2812bArray.led[3].dout: D9.2, D10.4
